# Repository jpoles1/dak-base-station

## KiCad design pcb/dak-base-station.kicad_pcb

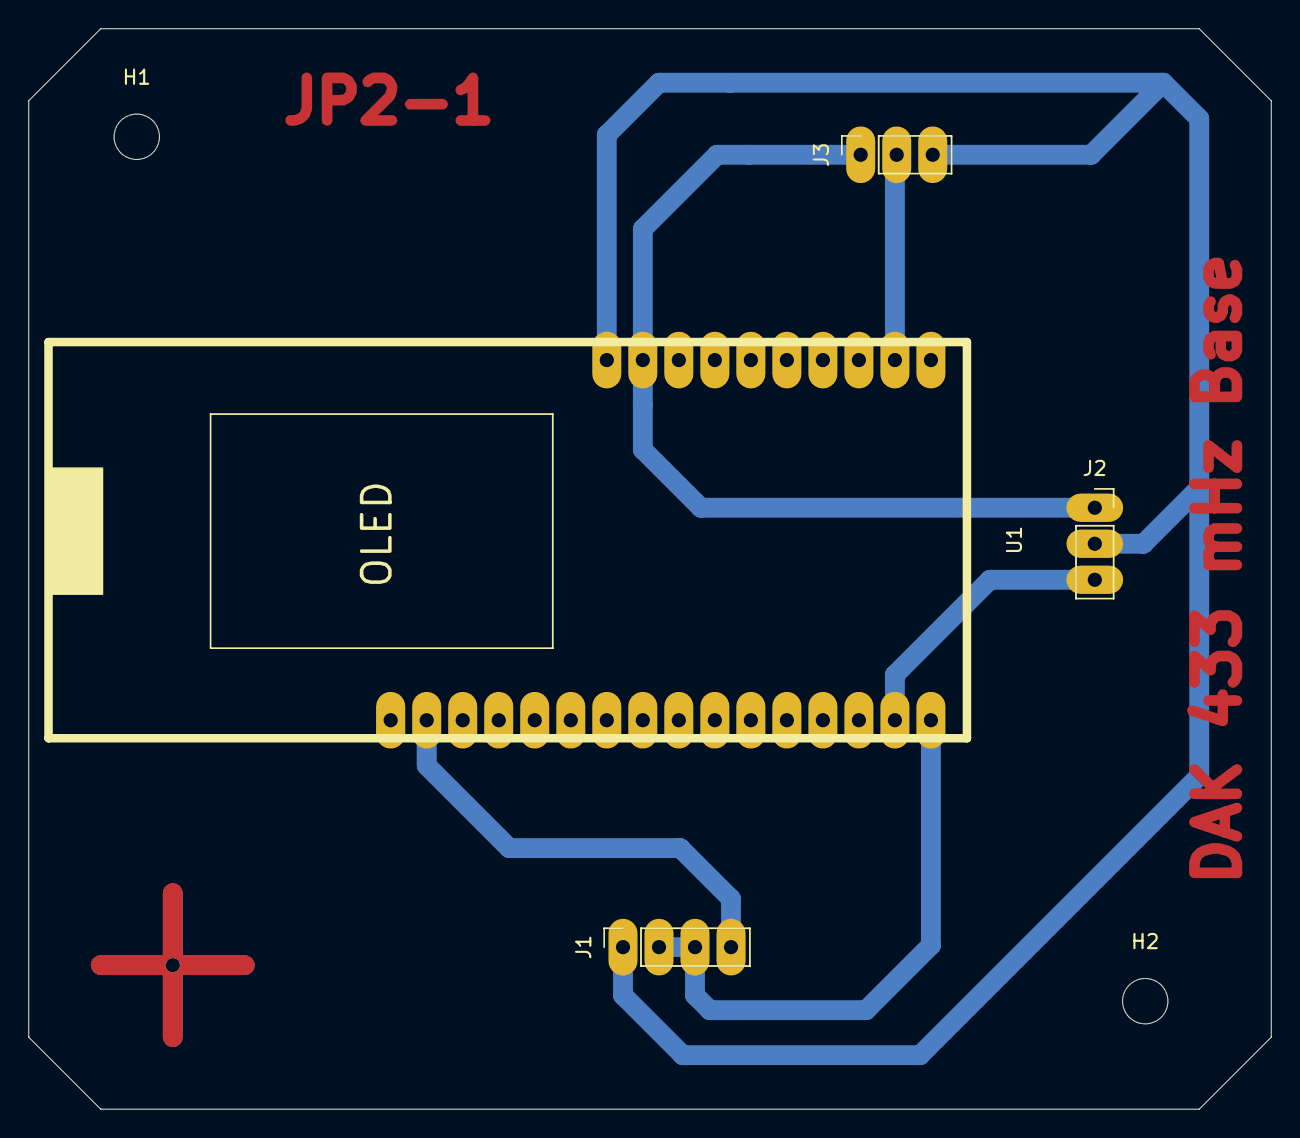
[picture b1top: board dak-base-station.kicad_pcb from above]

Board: 2 copper layers, 87.6 x 76.2 mm, 6 parts (0 on the bottom side), 6 nets.

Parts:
H1, H2: MountingHole; MountingHole_3.2mm_M3
J1: 433 mHz Receiver; 433Receiver
J2: 433 mHz Transmitter; PinSocket_1x03_P2.54mm_Vertical
J3: DHT11_Breakout; PinSocket_1x03_P2.54mm_Vertical
U1: ESP32-OLED; ESP32 OLED

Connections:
unnamed: J1.1, J2.2, J3.3, U1.26
unnamed: J1.2, J1.3, U1.16
unnamed: J1.4, U1.2
unnamed: J2.1, J3.1, U1.25
unnamed: J2.3, U1.15
unnamed: J3.2, U1.18

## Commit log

2018-10-02 DAK Servo blind controls working
2018-10-05 Fixing reset issue
2018-10-05 Adding brightness aliases
2019-01-11 Fixing up setup. Hopefully less crashes?
2019-04-06 Transmit codes in comments
2019-04-06 MAC Spoof
2019-04-25 Git ignoring
2019-04-25 Adding in PEAP authentication
2019-10-13 Added .pio to gitignore
2019-10-14 Got a great first go at PCB design, wanna move stuff tho
2019-10-20 PCB!
2019-10-20 Ping/pong functionality!
2019-10-25 Rust server upgrade
2019-10-25 Adapting to new websocket library!
2019-10-28 moving server room name to config
2020-08-02 New code
2020-08-02 Switching back to wpa2
